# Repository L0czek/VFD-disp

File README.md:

# IVLM3 driver board

This project was created to drive the old IVLM3-5/7 VFD displays. These tubes are tricolor 5×7 matrices that allow displaying arbitrary shapes, provided you stand far enough for the subpixels to blend. The board consists of several sections and is controlled via an ESP32-C6 module, which uses the HV5812 as the anode and grid driver. These tubes require anode voltages of up to 50V in pulse mode with 3V heating, so the board features a boost and buck converter to achieve these voltages.

**Assembled board.**  

**All pixels lit at 10V anode.**

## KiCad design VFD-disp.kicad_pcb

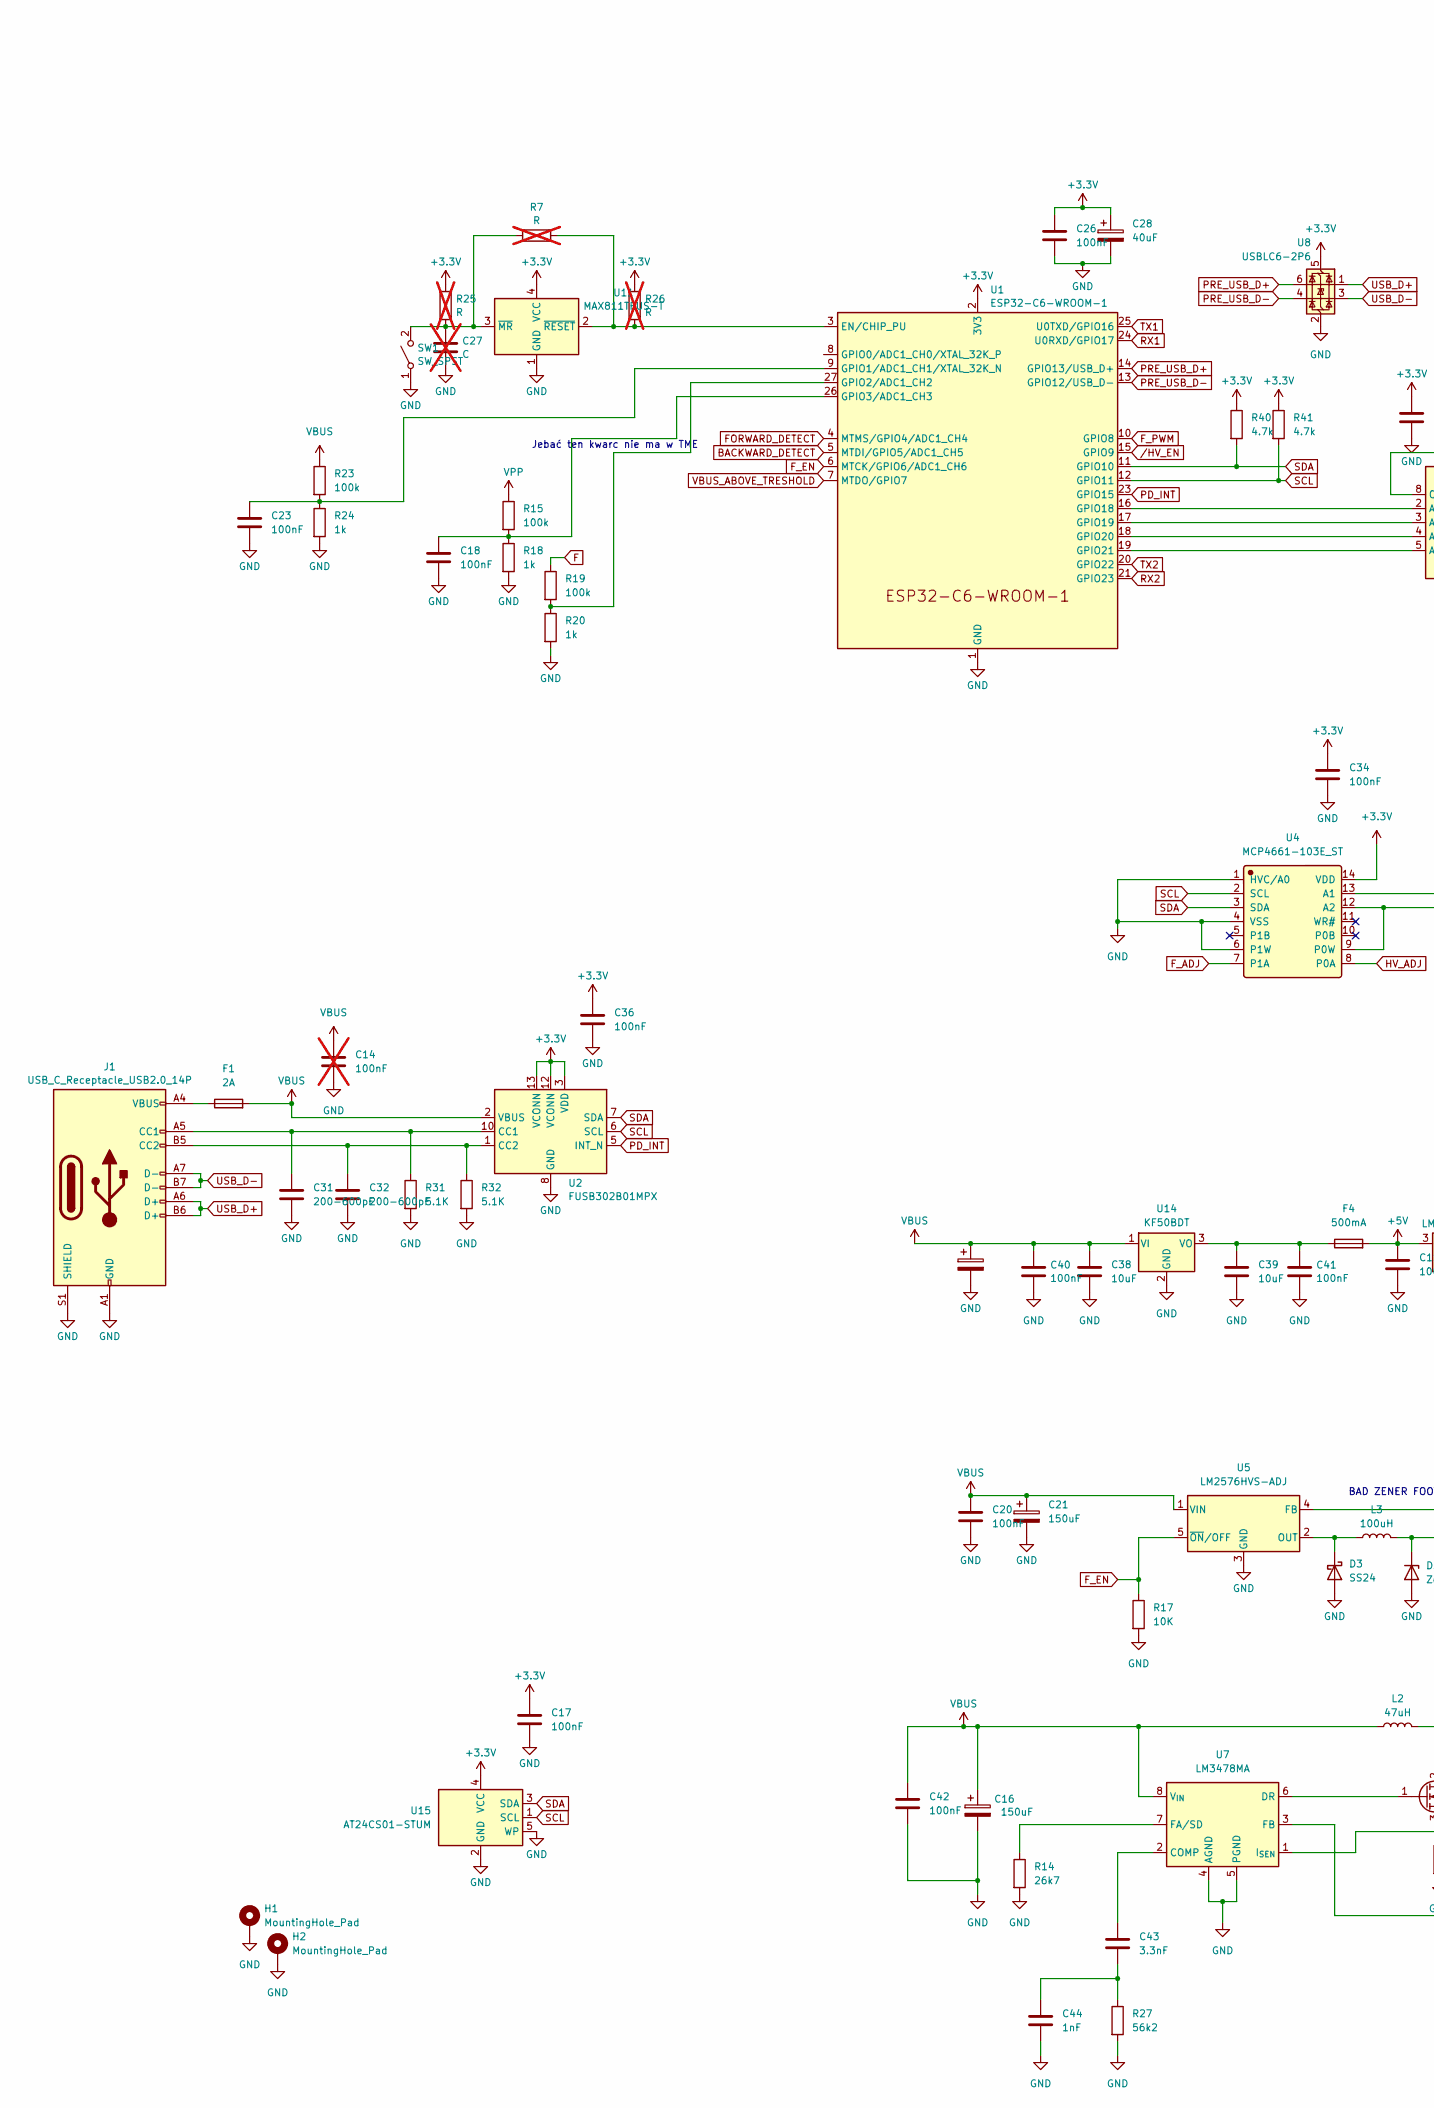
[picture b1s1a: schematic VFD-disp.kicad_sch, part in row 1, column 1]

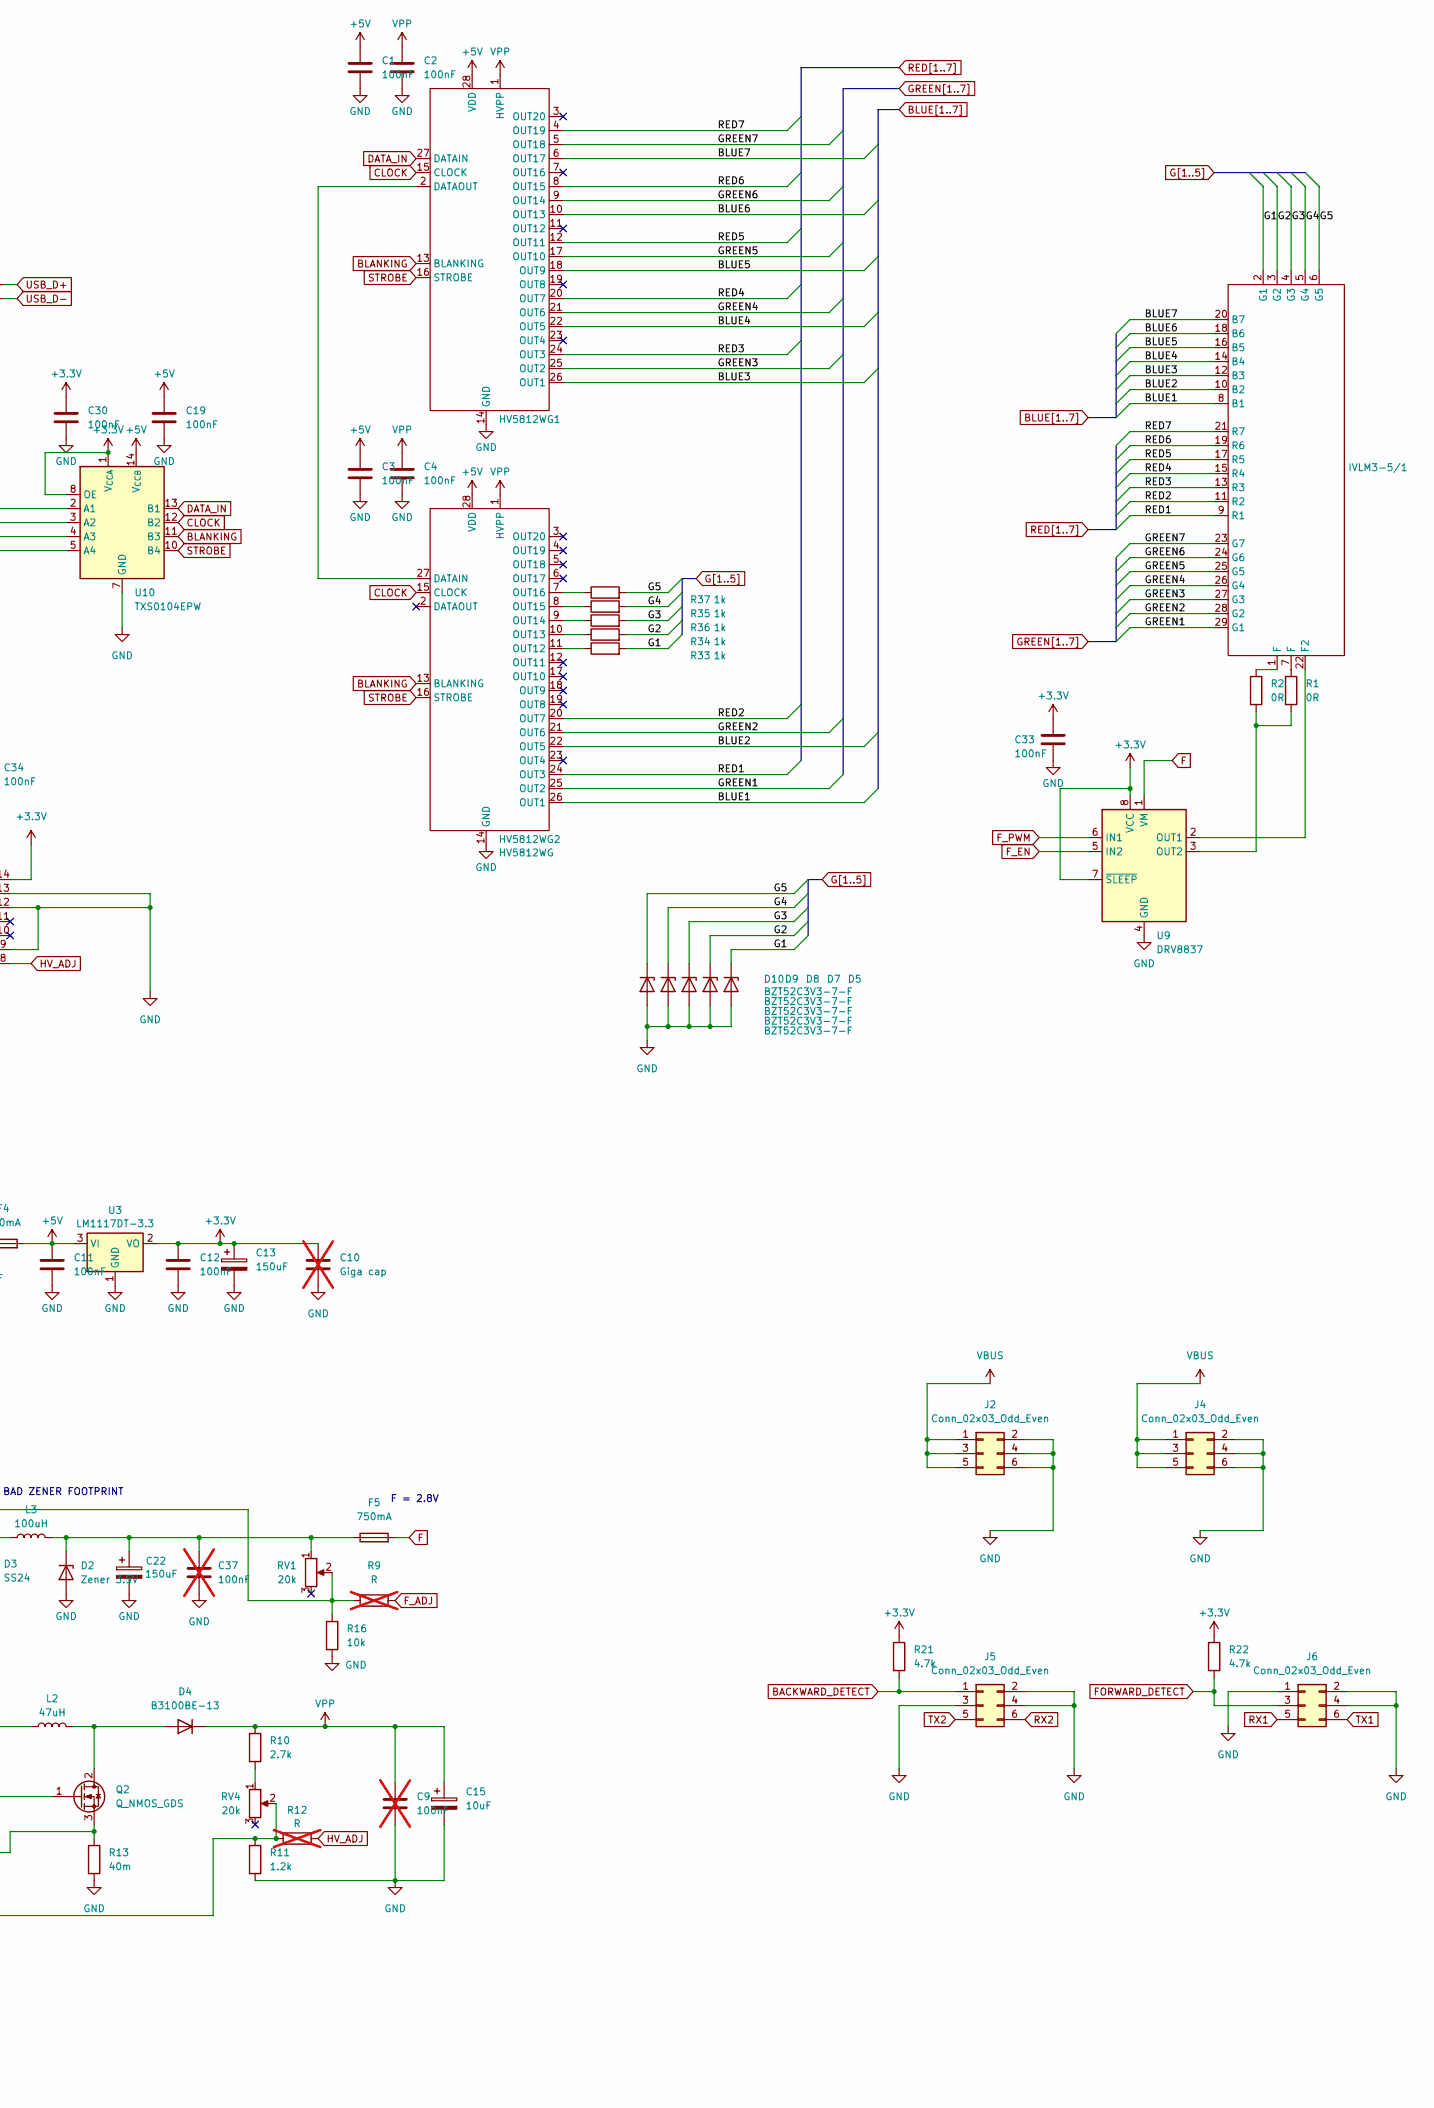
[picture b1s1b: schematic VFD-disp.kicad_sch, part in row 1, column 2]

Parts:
C1, C2, C3, C4, C11, C12, C17, C18, C19, C20, C23, C26, C30, C33, C34, C36, C40, C41, C42: 100nF; C_0805_2012Metric; LCSC C7419429
C9: 100nF; C_2220_5750Metric; LCSC C7419429; not fitted
C10: Giga cap; C_2220_5750Metric; not fitted
C13, C16, C21, C22, C24: 150uF; CP_Elec_5x4.5
C14, C37: 100nF; C_2220_5750Metric; not fitted
C15: 10uF; CP_Elec_5x4.5
C27: C; C_0805_2012Metric; not fitted
C28: 40uF; CP_EIA-7343-31_Kemet-D
C31, C32: 200-600pF; C_0805_2012Metric
C38, C39: 10uF; C_1206_3216Metric
C43: 3.3nF; C_0805_2012Metric
C44: 1nF; C_0805_2012Metric
D2: Zener 3.5V; D_SMB
D3: SS24; D_SMB; LCSC C7420362
D4: B3100BE-13; D_SMB
D5: BZT52C3V3-7-F; D_SOD-123
D7, D8, D9, D10: BZT52C3V3-7-F; D_SOD-123; LCSC C7420362
F1: 2A; Fuse_0805_2012Metric
F4: 500mA; Fuse_0805_2012Metric
F5: 750mA; Fuse_0805_2012Metric
H1, H2: MountingHole_Pad; MountingHole_2.2mm_M2_Pad_Via
HV5812WG1, HV5812WG2: HV5812WG; SOIC-28W_7.5x17.9mm_P1.27mm
IVLM3-5/1: IVLM3-5_7
J1: USB_C_Receptacle_USB2.0_14P; USB_C_Receptacle_G-Switch_GT-USB-7010ASV
J2, J5: Conn_02x03_Odd_Even; PinSocket_2x03_P2.54mm_Horizontal
J4, J6: Conn_02x03_Odd_Even; PinHeader_2x03_P2.54mm_Horizontal
L2: 47uH; C_2220_5750Metric
L3: 100uH; L_Bourns_SRP1038C_10.0x10.0mm
Q2: Q_NMOS_GDS; TO-252-2
R1, R2: 0R; R_0805_2012Metric; LCSC C7610430
R7, R9, R12, R25, R26: R; R_0805_2012Metric; not fitted
R10: 2.7k; R_0805_2012Metric
R11: 1.2k; R_0805_2012Metric
R13: 40m; R_0805_2012Metric
R14: 26k7; R_0805_2012Metric; LCSC C7319379
R15, R19, R23: 100k; R_0805_2012Metric; LCSC C7319379
R16: 10k; R_0805_2012Metric; LCSC C7319379
R17: 10K; R_0805_2012Metric; LCSC C7319379
R18, R20, R24, R33, R34, R35, R36, R37: 1k; R_0805_2012Metric; LCSC C6654733
R21, R22, R40, R41: 4.7k; R_0805_2012Metric; LCSC C7468408
R27: 56k2; R_0805_2012Metric; LCSC C6654733
R31, R32: 5.1K; R_0805_2012Metric
RV1, RV4: 20k; Potentiometer_Bourns_3269W_Vertical
SW1: SW_SPST; SW_SPST_B3S-1000
U1: ESP32-C6-WROOM-1
U2: FUSB302B01MPX; WQFN-14-1EP_2.5x2.5mm_P0.5mm_EP1.45x1.45mm
U3: LM1117DT-3.3; TO-252-3_TabPin2
U4: MCP4661-103E_ST; TSSOP-14_4.4x5mm_P0.65mm; Manufacturer Part MCP4661-103E/ST
U5: LM2576HVS-ADJ; TO-263-5_TabPin3; LCSC C7419972
U7: LM3478MA; SOIC-8_3.9x4.9mm_P1.27mm
U8: USBLC6-2P6; SOT-666
U9: DRV8837; WSON-8-1EP_2x2mm_P0.5mm_EP0.9x1.6mm
U10: TXS0104EPW; TSSOP-14_4.4x5mm_P0.65mm
U11: MAX811TEUS-T; SOT-143
U14: KF50BDT; TO-252-2
U15: AT24CS01-STUM; SOT-23-5

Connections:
+3.3V: C10.1, C12.1, C13.1, C17.1, C26.1, C28.1, C30.1, C33.1, C34.1, C36.1, R21.1, R22.1, R25.1, R26.1, R40.1, R41.1, U1.2 (3V3), U2.3 (VDD), U2.4 (VDD), U2.12 (VCONN), U2.13 (VCONN), U3.2 (VO), U4.14 (VDD), U8.5 (VBUS), U9.7 (~SLEEP), U9.8 (VCC), U10.1 (V_{CCA}), U10.8 (OE), U11.4 (VCC), U15.4 (VCC)
+5V: C1.1, C3.1, C11.1, C19.1, F4.2, HV5812WG1.28 (VDD), HV5812WG2.28 (VDD), U3.3 (VI), U10.14 (V_{CCB})
BACKWARD_DETECT: J5.1, R21.2, U1.5 (MTDI/GPIO5/ADC1_CH5)
BLANKING: HV5812WG1.13 (BLANKING), HV5812WG2.13 (BLANKING), U10.11 (B3)
BLUE1: HV5812WG2.26 (OUT1), IVLM3-5/1.8 (B1)
BLUE2: HV5812WG2.22 (OUT5), IVLM3-5/1.10 (B2)
BLUE3: HV5812WG1.26 (OUT1), IVLM3-5/1.12 (B3)
BLUE4: HV5812WG1.22 (OUT5), IVLM3-5/1.14 (B4)
BLUE5: HV5812WG1.18 (OUT9), IVLM3-5/1.16 (B5)
BLUE6: HV5812WG1.10 (OUT13), IVLM3-5/1.18 (B6)
BLUE7: HV5812WG1.6 (OUT17), IVLM3-5/1.20 (B7)
CLOCK: HV5812WG1.15 (CLOCK), HV5812WG2.15 (CLOCK), U10.12 (B2)
DATA_IN: HV5812WG1.27 (DATAIN), U10.13 (B1)
F: F5.2, R19.1, U9.1 (VM)
FORWARD_DETECT: J6.3, R22.2, U1.4 (MTMS/GPIO4/ADC1_CH4)
F_ADJ: R9.2, U4.7 (P1A)
F_EN: R17.1, U1.6 (MTCK/GPIO6/ADC1_CH6), U5.5 (~ON/OFF), U9.5 (IN2)
F_PWM: U1.10 (GPIO8), U9.6 (IN1)
G1: D5.1 (K), IVLM3-5/1.2 (G1), R33.2
G2: D7.1 (K), IVLM3-5/1.3 (G2), R34.2
G3: D8.1 (K), IVLM3-5/1.4 (G3), R36.2
G4: D9.1 (K), IVLM3-5/1.5 (G4), R35.2
G5: D10.1 (K), IVLM3-5/1.6 (G5), R37.2
GND: C1.2, C2.2, C3.2, C4.2, C9.2, C10.2, C11.2, C12.2, C13.2, C14.2, C15.2, C16.2, C17.2, C18.2, C19.2, C20.2, C21.2, C22.2, C23.2, C24.2, C26.2, C27.2, C28.2, C30.2, C31.2, C32.2, C33.2, C34.2, C36.2, C37.2, C38.2, C39.2, C40.2, C41.2, C42.2, C44.2, D2.2 (A), D3.2 (A), D5.2 (A), D7.2 (A), D8.2 (A), D9.2 (A), D10.2 (A), H1.1 (1_1), H2.1 (1_1), HV5812WG1.14 (GND), HV5812WG2.14 (GND), J1.A1 (GND), J1.A12 (GND), J1.B1 (GND), J1.B12 (GND), J1.S1 (SHIELD), J2.2, J2.4, J2.6, J4.2, J4.4, J4.6, J5.2, J5.3, J5.4, J6.1, J6.2, J6.4, R11.2, R13.2, R14.2, R16.2, R17.2, R18.2, R20.2, R24.2, R27.2, R31.2, R32.2, SW1.1 (A), U1.1 (GND), U1.28 (GND), U1.29 (GND), U2.8 (GND), U2.9 (GND), U2.15 (GND), U3.1 (GND), U4.1 (HVC/A0), U4.4 (VSS), U4.6 (P1W), U4.9 (P0W), U4.12 (A2), U4.13 (A1), U5.3 (GND), U7.4 (AGND), U7.5 (PGND), U8.2 (GND), U9.4 (GND), U9.9 (GND), U10.7 (GND), U11.1 (GND), U14.2 (GND), U15.2 (GND), U15.5 (WP)
GREEN1: HV5812WG2.25 (OUT2), IVLM3-5/1.29 (G1)
GREEN2: HV5812WG2.21 (OUT6), IVLM3-5/1.28 (G2)
GREEN3: HV5812WG1.25 (OUT2), IVLM3-5/1.27 (G3)
GREEN4: HV5812WG1.21 (OUT6), IVLM3-5/1.26 (G4)
GREEN5: HV5812WG1.17 (OUT10), IVLM3-5/1.25 (G5)
GREEN6: HV5812WG1.9 (OUT14), IVLM3-5/1.24 (G6)
GREEN7: HV5812WG1.5 (OUT18), IVLM3-5/1.23 (G7)
HV_ADJ: R12.2, U4.8 (P0A)
unnamed: C43.2, C44.1, R27.1
unnamed: C22.1, C37.1, D2.1 (K), F5.1, L3.2, RV1.1
unnamed: D3.1 (K), L3.1, U5.2 (OUT)
unnamed: D4.2 (A), L2.2, Q2.2 (D)
unnamed: F1.1, J1.A4 (VBUS), J1.A9 (VBUS), J1.B4 (VBUS), J1.B9 (VBUS)
unnamed: HV5812WG1.2 (DATAOUT), HV5812WG2.27 (DATAIN)
unnamed: HV5812WG2.11 (OUT12), R33.1
unnamed: HV5812WG2.10 (OUT13), R34.1
unnamed: HV5812WG2.9 (OUT14), R36.1
unnamed: HV5812WG2.8 (OUT15), R35.1
unnamed: HV5812WG2.7 (OUT16), R37.1
unnamed: IVLM3-5/1.22 (F2), U9.2 (OUT1)
unnamed: IVLM3-5/1.1 (F), R2.1
unnamed: IVLM3-5/1.7 (F), R1.1
unnamed: C31.1, J1.A5 (CC1), R31.1, U2.10 (CC1), U2.11 (CC1)
unnamed: C32.1, J1.B5 (CC2), R32.1, U2.1 (CC2), U2.14 (CC2)
unnamed: Q2.1 (G), U7.6 (DR)
unnamed: Q2.3 (S), R13.1, U7.1 (I_{SEN})
unnamed: R10.2, RV4.1
unnamed: C27.1, R7.1, R25.2, SW1.2 (B), U11.3 (~MR)
unnamed: R7.2, R26.2, U1.3 (EN/CHIP_PU), U11.2 (~RESET)
unnamed: C23.1, R23.2, R24.1, U1.9 (GPIO1/ADC1_CH1/XTAL_32K_N)
unnamed: R19.2, R20.1, U1.27 (GPIO2/ADC1_CH2)
unnamed: C18.1, R15.2, R18.1, U1.26 (GPIO3/ADC1_CH3)
unnamed: U1.16 (GPIO18), U10.2 (A1)
unnamed: U1.17 (GPIO19), U10.3 (A2)
unnamed: U1.18 (GPIO20), U10.4 (A3)
unnamed: U1.19 (GPIO21), U10.5 (A4)
unnamed: R9.1, R16.1, RV1.2, U5.4 (FB)
unnamed: C43.1, U7.2 (COMP)
unnamed: R14.1, U7.7 (FA/SD)
unnamed: R11.1, R12.1, RV4.2, U7.3 (FB)
unnamed: R1.2, R2.2, U9.3 (OUT2)
unnamed: C39.1, C41.1, F4.1, U14.3 (VO)
PD_INT: U1.23 (GPIO15), U2.5 (INT_N)
PRE_USB_D+: U1.14 (GPIO13/USB_D+), U8.6 (I/O1)
PRE_USB_D-: U1.13 (GPIO12/USB_D-), U8.4 (I/O2)
RED1: HV5812WG2.24 (OUT3), IVLM3-5/1.9 (R1)
RED2: HV5812WG2.20 (OUT7), IVLM3-5/1.11 (R2)
RED3: HV5812WG1.24 (OUT3), IVLM3-5/1.13 (R3)
RED4: HV5812WG1.20 (OUT7), IVLM3-5/1.15 (R4)
RED5: HV5812WG1.12 (OUT11), IVLM3-5/1.17 (R5)
RED6: HV5812WG1.8 (OUT15), IVLM3-5/1.19 (R6)
RED7: HV5812WG1.4 (OUT19), IVLM3-5/1.21 (R7)
RX1: J6.5, U1.24 (U0RXD/GPIO17)
RX2: J5.6, U1.21 (GPIO23)
SCL: R41.2, U1.12 (GPIO11), U2.6 (SCL), U4.2 (SCL), U15.1 (SCL)
SDA: R40.2, U1.11 (GPIO10), U2.7 (SDA), U4.3 (SDA), U15.3 (SDA)
STROBE: HV5812WG1.16 (STROBE), HV5812WG2.16 (STROBE), U10.10 (B4)
TX1: J6.6, U1.25 (U0TXD/GPIO16)
TX2: J5.5, U1.20 (GPIO22)
USB_D+: J1.A6 (D+), J1.B6 (D+), U8.1 (I/O1)
USB_D-: J1.A7 (D-), J1.B7 (D-), U8.3 (I/O2)
VBUS: C14.1, C16.1, C20.1, C21.1, C24.1, C38.1, C40.1, C42.1, F1.2, J2.1, J2.3, J2.5, J4.1, J4.3, J4.5, L2.1, R23.1, U2.2 (VBUS), U5.1 (VIN), U7.8 (V_{IN}), U14.1 (VI)
VBUS_ABOVE_TRESHOLD: U1.7 (MTDO/GPIO7)
VPP: C2.1, C4.1, C9.1, C15.1, D4.1 (K), HV5812WG1.1 (HVPP), HV5812WG2.1 (HVPP), R10.1, R15.1
/HV_EN: U1.15 (GPIO9)

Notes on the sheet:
F = 2.8V
Jebać ten kwarc nie ma w TME
BAD ZENER FOOTPRINT

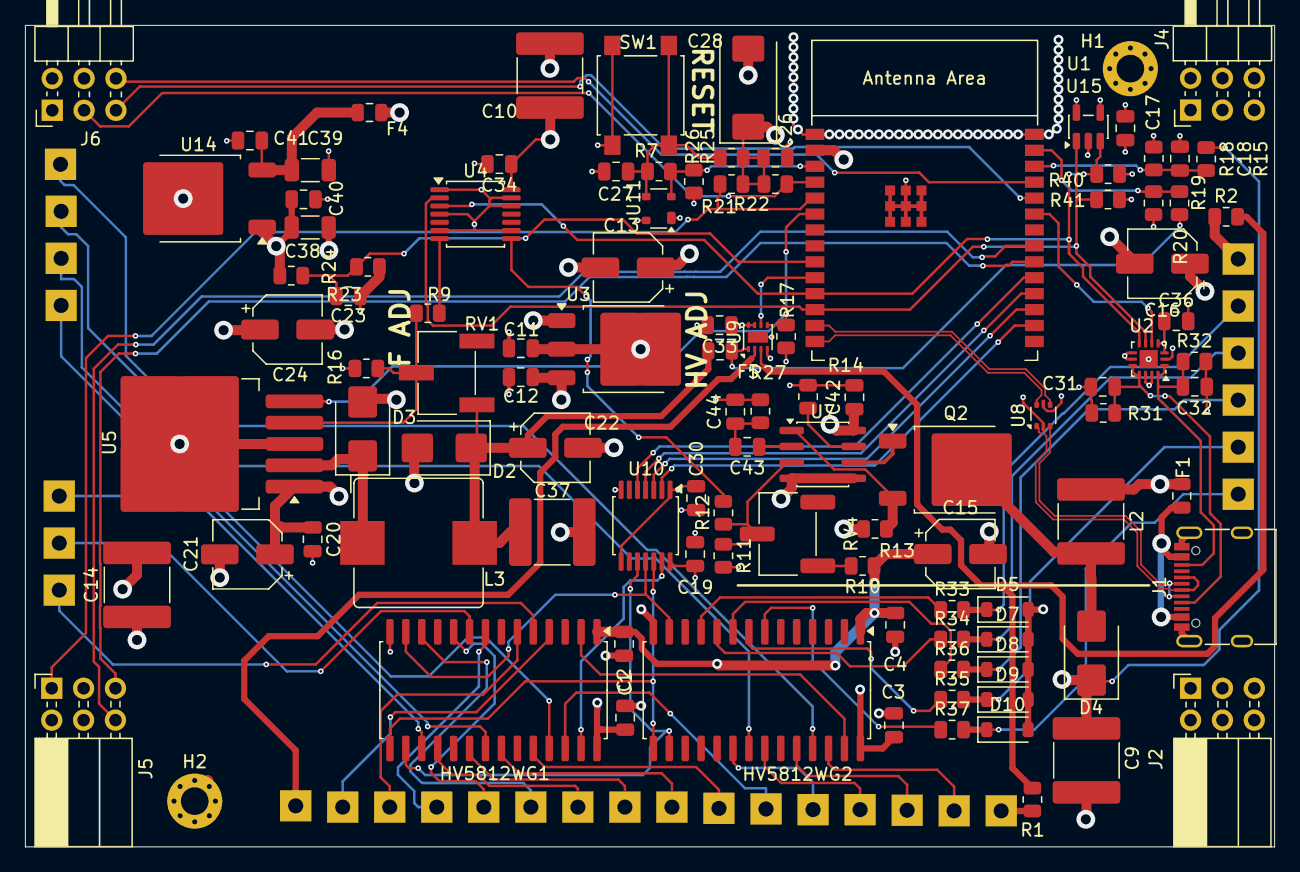
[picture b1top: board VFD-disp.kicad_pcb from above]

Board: 4 copper layers, 99.6 x 65.5 mm, 107 parts (1 on the bottom side), 87 nets.

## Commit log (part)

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2026-03-13 Initial
2026-03-13 Make schematic ready for routing
2026-03-14 WIP płytka
2026-03-16 WIP all components placed
2026-03-16 WIP connecting...
2026-03-16 All Connected!
2026-03-17 We need to golf!
2026-03-18 Reroute pcb
2026-03-18 Add chonky cermaics caps to be safe...
2026-03-26 Finish pcb
2026-03-29 Add mounting holes and some rework
2026-04-06 Fix DRC errors
2026-04-06 Add CC lines pull down
2026-04-06 Fix screw connections
2026-05-21 Fix docking connectors reroute usb
2026-05-23 Fix silkscreen and plot gerber
